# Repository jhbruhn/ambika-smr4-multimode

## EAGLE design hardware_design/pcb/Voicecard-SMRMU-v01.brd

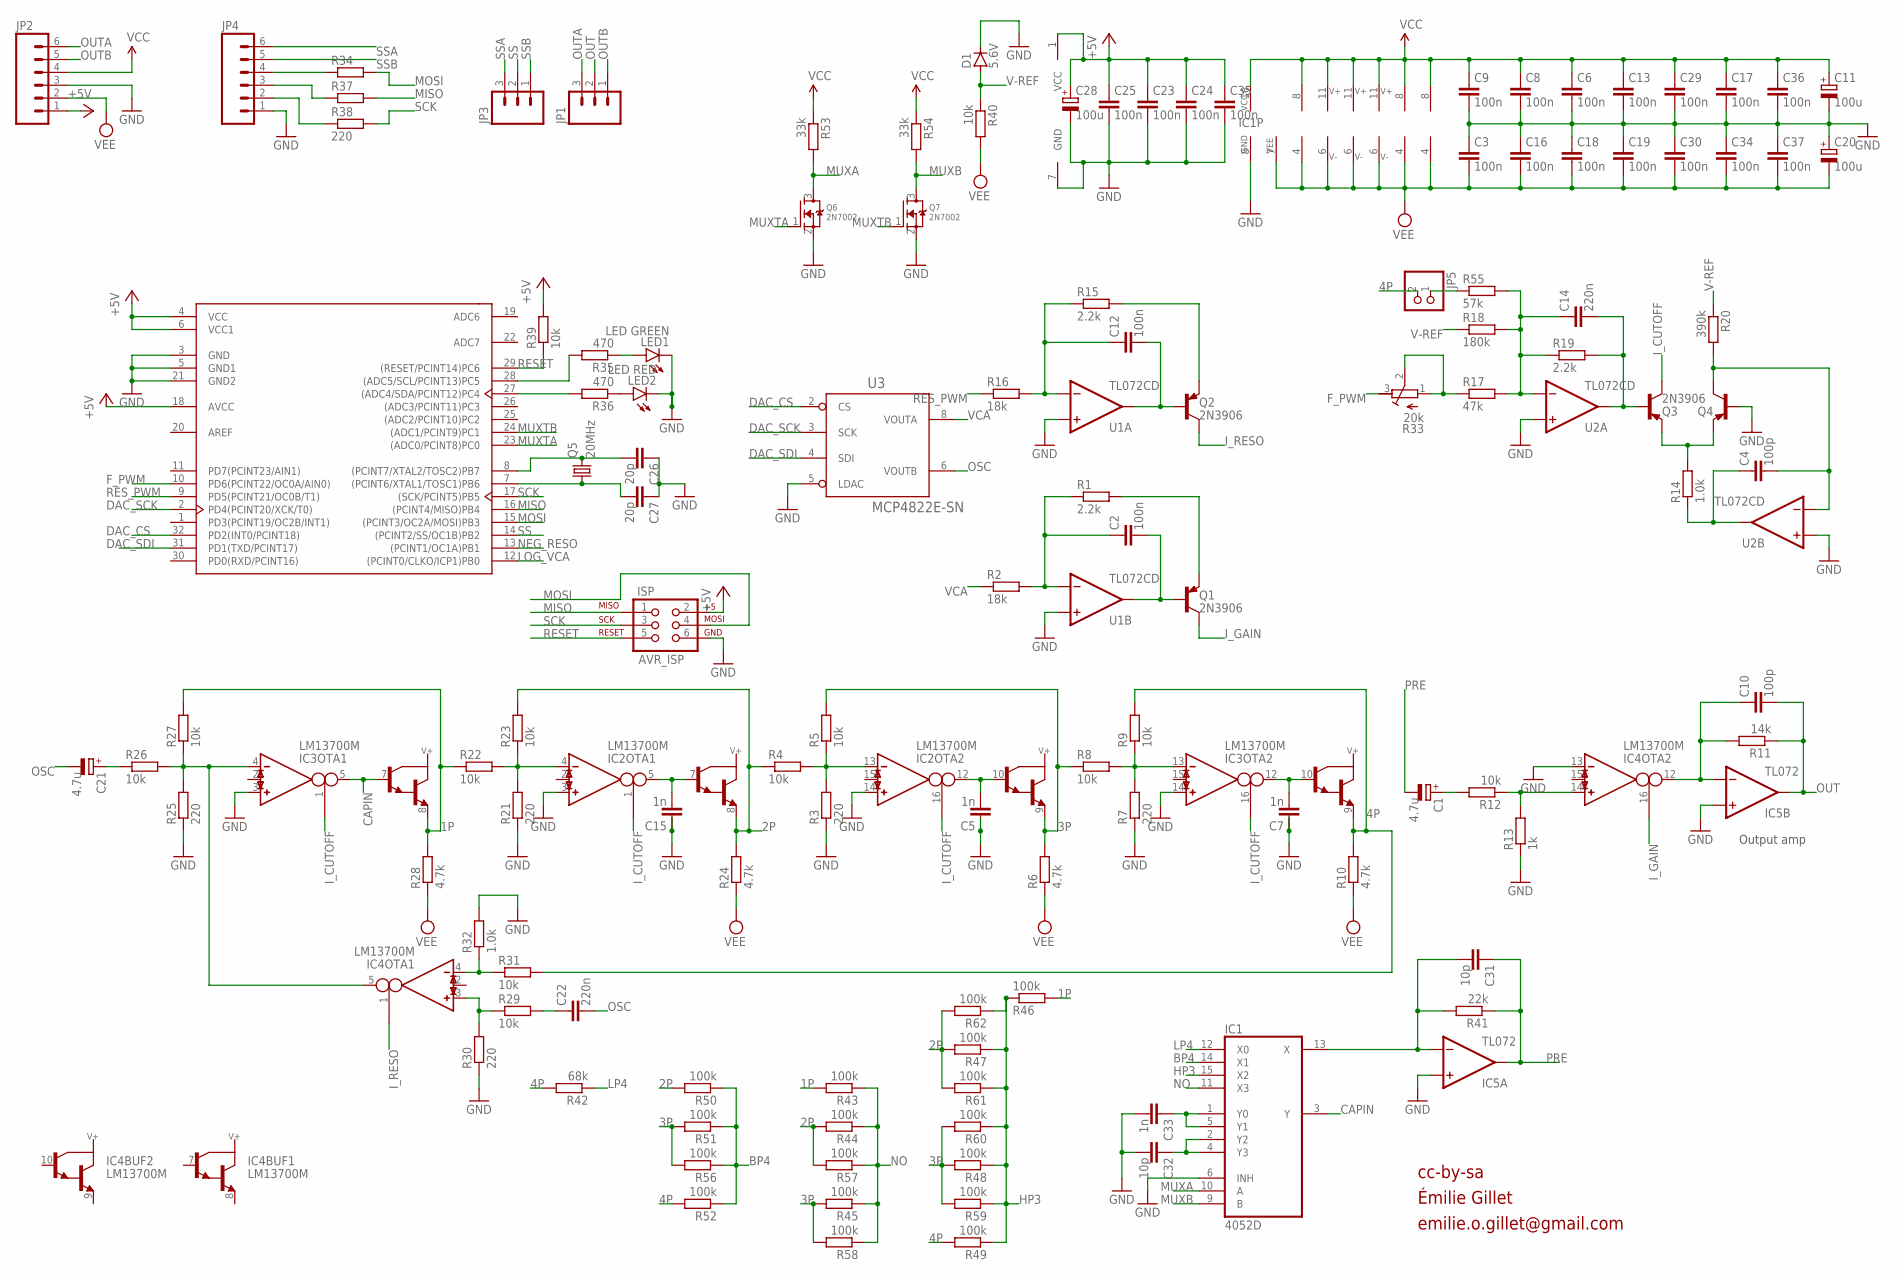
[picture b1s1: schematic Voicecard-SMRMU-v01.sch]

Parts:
C1, C21: 4.7u; UD-5X5,8_NICHICON
C2, C3, C6, C8, C9, C12, C13, C16, C17, C18, C19, C23, C24, C25, C29, C30, C34, C35, C36, C37: 100n; C0603
C4, C10: 100p; C0603
C5, C7, C15, C33: 1n; C0603
C11, C20, C28: 100u; UD-6,3X7,7_NICHICON
C14, C22: 220n; C0603
C26, C27: 20p; C0603
C31, C32: 10p; C0603
D1: 5.6V; MELF-MLL34
IC1: 4052D; SOIC16N
IC2, IC3, IC4: LM13700M; SO16
IC5: TL072; SOIC8
ISP: AVR_ISP; 2X3
JP1, JP3: M03PTH; 1X03
JP2, JP4: M06SIP; 1X06
JP5: PINHD-1X2; 1X02
LED1: LED GREEN; CHIP-LED0603
LED2: LED RED; CHIP-LED0603
Q1, Q2, Q3, Q4: 2N3906; SOT23-BEC
Q5: 20MHz; HC49UP
Q6, Q7: 2N7002; SOT23
R1, R15, R19: 2.2k; R0603
R2, R16: 18k; R0603
R3, R7, R21, R25, R30, R34, R37, R38: 220; R0603
R4, R5, R8, R9, R12, R22, R23, R26, R27, R29, R31, R39, R40: 10k; R0603
R6, R10, R24, R28: 4.7k; R0603
R11: 14k; R0603
R13: 1k; R0603
R14, R32: 1.0k; R0603
R17: 47k; R0603
R18: 180k; R0603
R20: 390k; R0603
R33: 20k; RTRIM3296P
R35, R36: 470; R0603
R41: 22k; R0603
R42: 68k; R0603
R43, R44, R45, R46, R47, R48, R49, R50, R51, R52, R56, R57, R58, R59, R60, R61, R62: 100k; R0603
R53, R54: 33k; R0603
R55: 57k; R0603
U1, U2: TL072CD; SOIC8
U3: MCP4822E-SN; SOIC8
U4: ATMEGA328P-AU; TQFP-32

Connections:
1P: IC3.8 (E), R22.1, R27.2, R28.2, R43.2, R46.2
2P: IC2.8 (E), R4.1, R23.2, R24.2, R44.2, R47.2, R50.2, R57.2, R61.2, R62.2
3P: IC2.9 (E), R5.2, R6.2, R8.1, R45.2, R48.2, R51.2, R56.2, R58.2, R59.2, R60.2
4P: IC3.9 (E), JP5.2, R9.2, R10.2, R31.2, R42.2, R49.2, R52.2
+5V: C23.1, C24.1, C25.1, C28.+, C35.1, ISP.2, JP2.1, R39.2, U3.1 (VCC), U4.4 (VCC), U4.6 (VCC1), U4.18 (AVCC)
AREF: U4.20 (AREF)
BP4: IC1.14 (X1), R50.1, R51.1, R52.1, R56.1
CAPIN: IC1.3 (Y), IC3.5 (OUT), IC3.7 (B)
DAC_CS: U3.2 (CS), U4.32 (PD2(INT0/PCINT18))
DAC_SCK: U3.3 (SCK), U4.2 (PD4(PCINT20/XCK/T0))
DAC_SDI: U3.4 (SDI), U4.31 (PD1(TXD/PCINT17))
F_PWM: R33.3 (E), U4.10 (PD6(PCINT22/OC0A/AIN0))
GND: C3.1, C5.1, C6.2, C7.1, C8.2, C9.2, C11.-, C13.2, C15.1, C16.1, C17.2, C18.1, C19.1, C20.+, C23.2, C24.2, C25.2, C26.1, C27.1, C28.-, C29.2, C30.1, C32.2, C33.2, C34.1, C35.2, C36.2, C37.1, D1.1 (C), IC1.6 (INH), IC1.8 (GND), IC2.3 (IN_P), IC2.14 (IN_P), IC3.3 (IN_P), IC3.14 (IN_P), IC4.13 (IN_N), IC5.3 (+IN), IC5.5 (+IN), ISP.6, JP2.3, JP4.1, LED1.C, LED2.C, Q4.B, Q6.2 (S), Q7.2 (S), R3.1, R7.1, R13.1, R21.1, R25.1, R30.1, R32.2, U1.3 (+IN), U1.5 (+IN), U2.3 (+IN), U2.5 (+IN), U3.5 (LDAC), U3.7 (GND), U4.3 (GND), U4.5 (GND1), U4.21 (GND2)
HP3: IC1.15 (X2), R46.1, R47.1, R48.1, R49.1, R59.1, R60.1, R61.1, R62.1
I_CUTOFF: IC2.1 (I_BIAS), IC2.16 (I_BIAS), IC3.1 (I_BIAS), IC3.16 (I_BIAS), Q3.C
I_GAIN: IC4.16 (I_BIAS), Q1.C
I_RESO: IC4.1 (I_BIAS), Q2.C
LOG_VCA: U4.12 ((PCINT0/CLKO/ICP1)PB0)
LP4: IC1.12 (X0), R42.1
MISO: ISP.1, R37.2, U4.16 ((PCINT4/MISO)PB4)
MOSI: ISP.4, R34.2, U4.15 ((PCINT3/OC2A/MOSI)PB3)
MUXA: IC1.10 (A), Q6.3 (D), R53.2
MUXB: IC1.9 (B), Q7.3 (D), R54.2
MUXTA: Q6.1 (G), U4.23 ((ADC0/PCINT8)PC0)
MUXTB: Q7.1 (G), U4.24 ((ADC1/PCINT9)PC1)
unnamed: Q3.E, Q4.E, R14.2
unnamed: C14.2, Q3.B, R19.2, U2.1 (OUT)
unnamed: C27.2, Q5.1, U4.7 ((PCINT6/XTAL1/TOSC1)PB6)
unnamed: C4.2, Q4.C, R20.2, U2.6 (-IN)
unnamed: C21.+, R26.1
unnamed: C33.1, IC1.1 (Y0), IC1.5 (Y1)
unnamed: LED1.A, R35.1
unnamed: JP4.2, R38.1
unnamed: C4.1, R14.1, U2.7 (OUT)
unnamed: LED2.A, R36.1
unnamed: R36.2, U4.27 ((ADC4/SDA/PCINT12)PC4)
unnamed: IC3.4 (IN_N), IC4.5 (OUT), R25.2, R26.2, R27.1
unnamed: JP4.3, R37.1
unnamed: C26.2, Q5.2, U4.8 ((PCINT7/XTAL2/TOSC2)PB7)
unnamed: C31.2, IC1.13 (X), IC5.2 (-IN), R41.2
unnamed: IC2.4 (IN_N), R21.2, R22.2, R23.1
unnamed: JP4.4, R34.1
unnamed: C15.2, IC2.5 (OUT), IC2.7 (B)
unnamed: R35.2, U4.28 ((ADC5/SCL/PCINT13)PC5)
unnamed: IC2.13 (IN_N), R3.2, R4.2, R5.1
unnamed: C32.1, IC1.2 (Y2), IC1.4 (Y3)
unnamed: C5.2, IC2.10 (B), IC2.12 (OUT)
unnamed: IC3.13 (IN_N), R7.2, R8.2, R9.1
unnamed: JP5.1, R55.1
unnamed: C1.+, R12.2
unnamed: C7.2, IC3.10 (B), IC3.12 (OUT)
unnamed: IC4.4 (IN_N), R31.1, R32.1
unnamed: C12.2, Q2.B, U1.1 (OUT)
unnamed: C2.2, Q1.B, U1.7 (OUT)
unnamed: C22.1, R29.2
unnamed: IC4.3 (IN_P), R29.1, R30.2
unnamed: IC4.14 (IN_P), R12.1, R13.2
unnamed: C14.1, R17.2, R18.2, R19.1, R55.2, U2.2 (-IN)
unnamed: R17.1, R33.1 (A), R33.2 (S)
unnamed: C2.1, R1.1, R2.2, U1.6 (-IN)
unnamed: C12.1, R15.1, R16.2, U1.2 (-IN)
unnamed: Q2.E, R15.2
unnamed: Q1.E, R1.2
unnamed: C10.1, IC4.12 (OUT), IC5.6 (-IN), R11.2
NEG_RESO: U4.13 ((PCINT1/OC1A)PB1)
NO: IC1.11 (X3), R43.1, R44.1, R45.1, R57.1, R58.1
OSC: C21.-, C22.2, U3.6 (VOUTB)
OUT: C10.2, IC5.7 (OUT), JP1.2, R11.1
OUTA: JP1.3, JP2.6
OUTB: JP1.1, JP2.5
PRE: C1.-, C31.1, IC5.1 (OUT), R41.1
RESET: ISP.5, R39.1, U4.29 ((RESET/PCINT14)PC6)
RES_PWM: R16.1, U4.9 (PD5(PCINT21/OC0B/T1))
SCK: ISP.3, R38.2, U4.17 ((SCK/PCINT5)PB5)
SS: JP3.2, U4.14 ((PCINT2/SS/OC1B)PB2)
SSA: JP3.3, JP4.6
SSB: JP3.1, JP4.5
V-REF: D1.2 (A), R18.1, R20.1, R40.1
VCA: R2.1, U3.8 (VOUTA)
VCC: C6.1, C8.1, C9.1, C11.+, C13.1, C17.1, C29.1, C36.1, IC1.16 (VCC), IC2.11 (V+), IC3.11 (V+), IC4.11 (V+), IC5.8 (V+), JP2.4, R53.1, R54.1, U1.8 (V+), U2.8 (V+)
VEE: C3.2, C16.2, C18.2, C19.2, C20.-, C30.2, C34.2, C37.2, IC1.7 (VEE), IC2.6 (V-), IC3.6 (V-), IC4.6 (V-), IC5.4 (V-), JP2.2, R6.1, R10.1, R24.1, R28.1, R40.2, U1.4 (V-), U2.4 (V-)

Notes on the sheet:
cc-by-sa
Output amp
Émilie Gillet
emilie.o.gillet@gmail.com

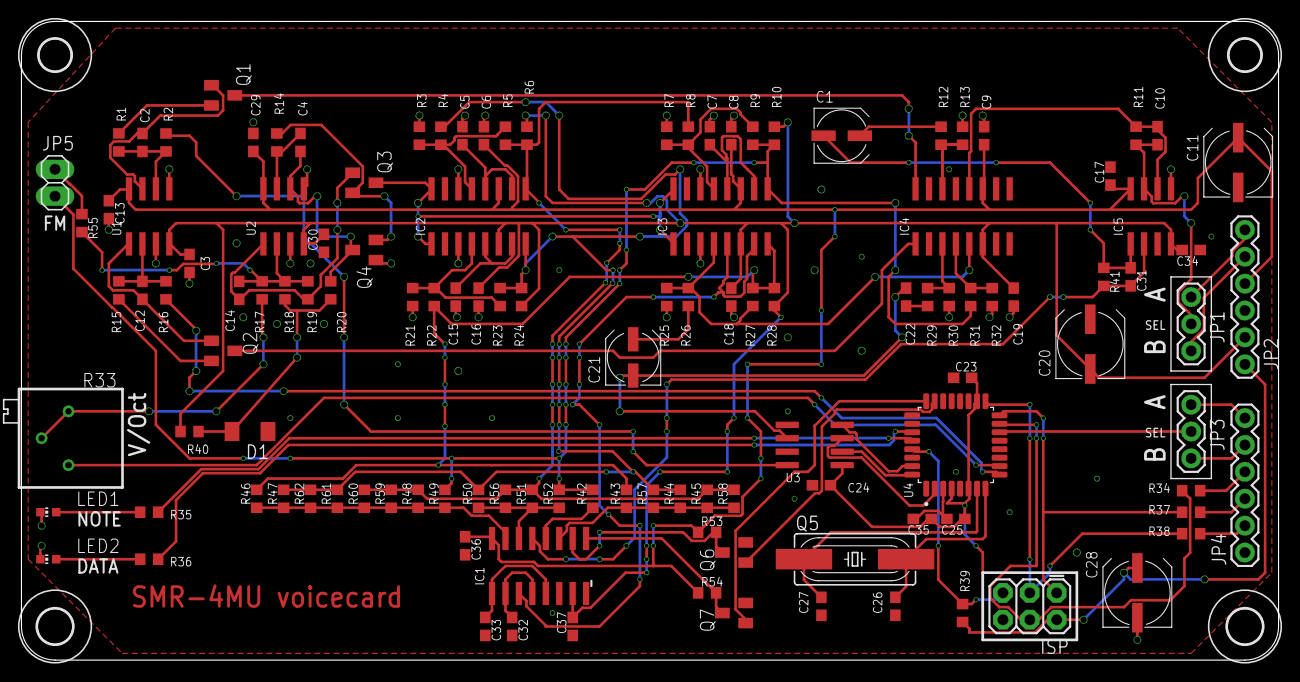
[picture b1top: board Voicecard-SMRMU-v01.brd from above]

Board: 2 copper layers, 118.7 x 60.3 mm, 128 parts (0 on the bottom side), 78 nets.

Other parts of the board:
U$1, U$2: 3,0
U$4, U$5: 3,3

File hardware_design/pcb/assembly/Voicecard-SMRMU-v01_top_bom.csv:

Comment,Designator,Footprint,LCSC Part #
1.0k,R14 R32,R0603,
1k,R13,R0603,
1n,C5 C7 C15 C33,C0603,
2.2k,R1 R15 R19,R0603,
2N3906,Q1 Q2 Q3 Q4,SOT23-BEC,
2N7002,Q6 Q7,SOT23,
4.7k,R6 R10 R24 R28,R0603,
4.7u,C1,UD-5X5 8_NICHICON,
4.7u,C21,UD-5X5 8_NICHICON,
5.6V,D1,MELF-MLL34,
10k,R4 R5 R8 R9 R12 R22 R23 R26 R27 R29 R31 R39 R40,R0603,
10p,C31 C32,C0603,
14k,R11,R0603,
18k,R2 R16,R0603,
20MHz,Q5,HC49UP,
20p,C26 C27,C0603,
22k,R41,R0603,
33k,R53 R54,R0603,
47k,R17,R0603,
57k,R55,R0603,
68k,R42,R0603,
100k,R43 R44 R45 R46 R47 R48 R49 R50 R51 R52 R56 R57 R58 R59 R60 R61 R62,R0603,
100n,C2 C3 C6 C8 C9 C12 C13 C16 C17 C18 C19 C23 C24 C25 C29 C30 C34 C35 C36 C37,C0603,
100p,C4 C10,C0603,
100u,C11,UD-6 3X7 7_NICHICON,
100u,C20,UD-6 3X7 7_NICHICON,
100u,C28,UD-6 3X7 7_NICHICON,
180k,R18,R0603,
220,R3 R7 R21 R25 R30 R34 R37 R38,R0603,
220n,C14 C22,C0603,
390k,R20,R0603,
470,R35 R36,R0603,
4052D,IC1,SOIC16N,
ATMEGA328P-AU,U4,TQFP-32,
LED GREEN,LED1,CHIP-LED0603,
LED RED,LED2,CHIP-LED0603,
LM13700M,IC2 IC3 IC4,SO16,
MCP4822E-SN,U3,SOIC8,
TL072,IC5,SOIC8,
TL072CD,U1 U2,SOIC8,

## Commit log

2020-09-21 Add simulated circuit pdf
2020-09-21 Add Schematic files
2020-09-23 Add boardlayout, assemblyfiles for v01 and pdf
2020-10-10 hardware revision 2, fixes mode ordering, improves PCB design, adds cutoff offset tuning
2020-10-11 Update hardware design with new Q1 position
2020-10-14 Update PCB with new pattern and optimized placements
2020-12-05 Layout optimizations
2020-12-05 Update stmlib
2020-12-07 Add cure
2020-12-07 Remove curve
2021-04-02 Fix Multiplexer BOM Entry to use proper CMOS variant
2021-04-09 Move ISP Header to the left for improved clearance to the capacitor next to it. Fixes #2
